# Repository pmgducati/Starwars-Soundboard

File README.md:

# Starwars-Soundboard
Arduino Soundboard using the MusicMaker Shield, Trellis and Arduino

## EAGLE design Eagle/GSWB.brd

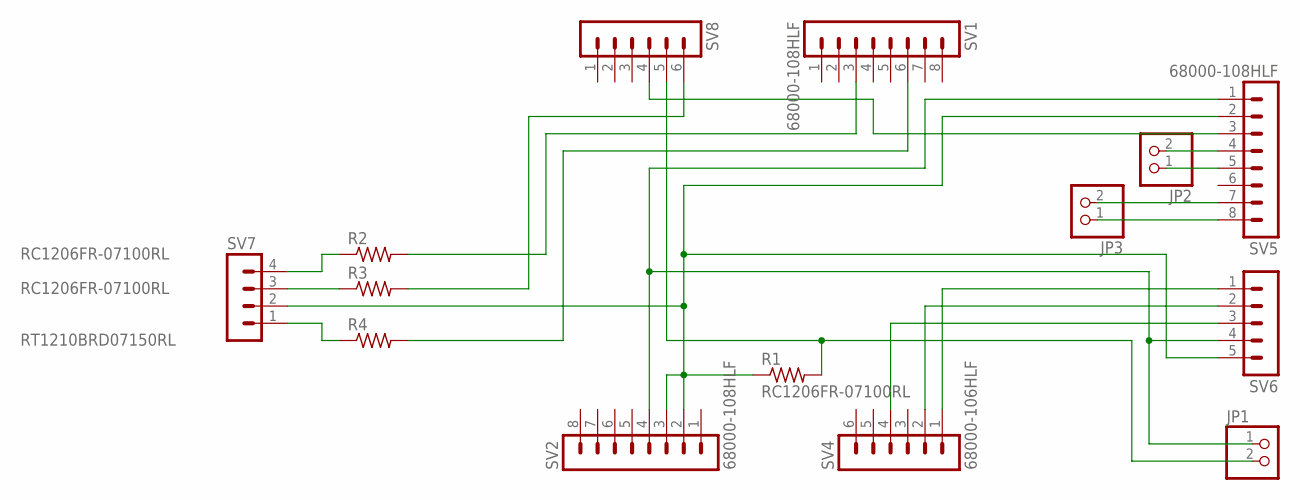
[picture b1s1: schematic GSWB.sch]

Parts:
JP1, JP2, JP3: PINHD-1X2; 1X02
R1, R2, R3: RC1206FR-07100RL; M1206
R4: RT1210BRD07150RL; M1206
SV1, SV2, SV5: 68000-108HLF; MA08-1
SV4: 68000-106HLF; MA06-1
SV6: MA05-1
SV7: MA04-1
SV8: MA06-1

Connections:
EN_GND: JP1.1, SV2.4, SV5.1, SV6.4
GND: R1.1, SV2.2, SV2.3, SV5.2, SV6.5, SV7.2
unnamed: JP3.2, SV5.7
unnamed: R3.1, SV7.3
unnamed: R2.1, SV7.4
unnamed: R3.2, SV8.6
unnamed: R2.2, SV1.3
unnamed: R4.2, SV1.6
unnamed: JP2.2, SV5.4
unnamed: SV4.1, SV6.1
unnamed: JP2.1, SV5.5
unnamed: SV4.2, SV6.2
unnamed: SV4.4, SV6.3
unnamed: JP3.1, SV5.8
unnamed: R4.1, SV7.1
unnamed: SV5.3, SV8.4
SW5V: JP1.2, R1.2, SV8.5

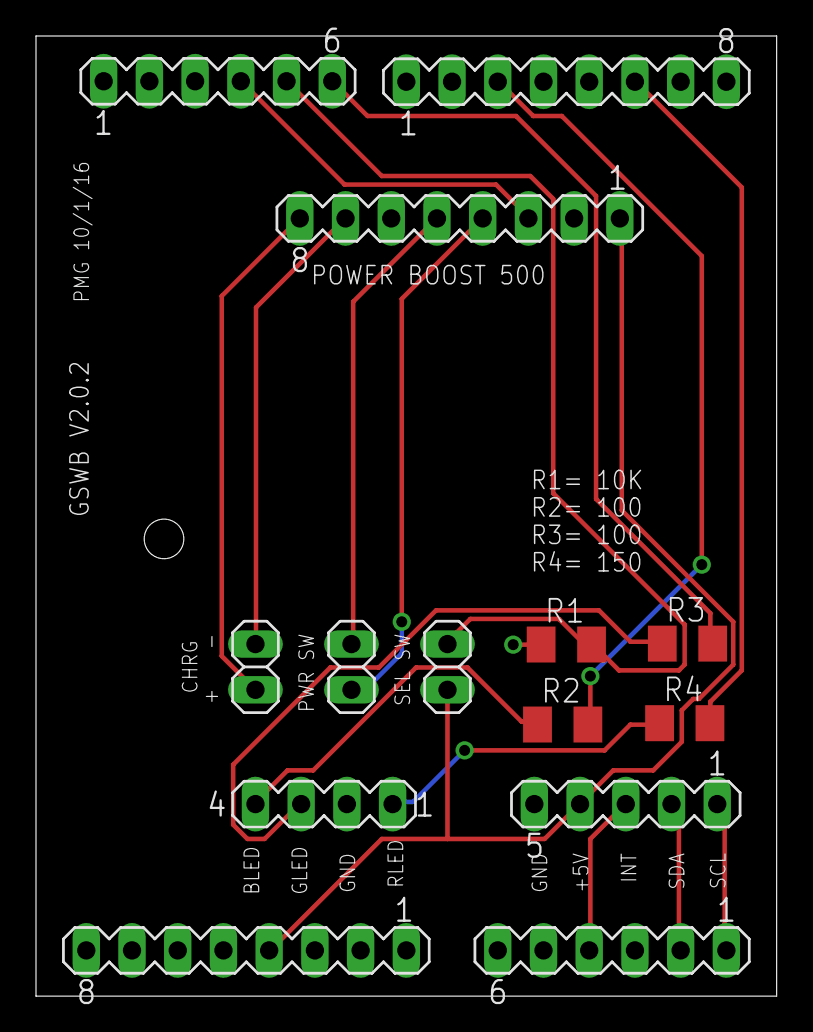
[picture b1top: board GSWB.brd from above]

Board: 2 copper layers, 41.1 x 53.3 mm, 14 parts (0 on the bottom side), 17 nets.

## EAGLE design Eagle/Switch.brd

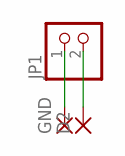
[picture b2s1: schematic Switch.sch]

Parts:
D2: 2,15/1,0
GND: 2,15/1,0
JP1: PINHD-1X2; 1X02

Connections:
unnamed: GND.1, JP1.1
unnamed: D2.1, JP1.2

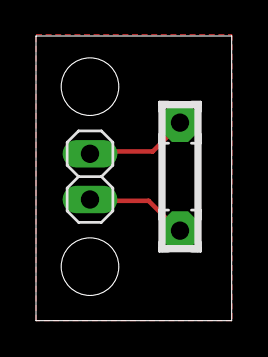
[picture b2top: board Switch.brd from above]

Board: 2 copper layers, 10.9 x 15.8 mm, 3 parts (0 on the bottom side), 2 nets.

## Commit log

2016-08-07 Initial Upload
2016-08-08 Added MP3 Shield Code from example back in to bring sound functionality back
2016-08-08 File Cleanup
2016-09-01 Cleaned House
    All Files have been sorted and 3 more modes of sounds added, Also
    cleaned up the code and finall got around to adding comments,
2016-09-01 Adding auto shutdown functionality
    Via MOSFETS
2016-09-26 Changes
    Removed Auto Sutdown , added shutdown notification, adding eagle files
    for for shield, LED and shield holders.
2016-09-26 updated Gerber files
    Added trace from lbat to D10
2016-09-26 Adding extra sounds not used in current build
    could be implemented in future
2016-11-24 Adding CAD Files
2016-11-24 gerber
2016-12-12 STL Files for Printing
    Addded STL Files
